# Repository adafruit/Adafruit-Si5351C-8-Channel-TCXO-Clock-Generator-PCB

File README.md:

## Adafruit Si5351C 8 Channel TCXO Clock Generator - 2.5KHz-200MHz - STEMMA QT PCB

<a href="http://www.adafruit.com/products/6534"><br/>
Click here to purchase one from the Adafruit shop</a>

PCB files for the Adafruit Si5351C 8 Channel TCXO Clock Generator - 2.5KHz-200MHz - STEMMA QT. 

Format is EagleCAD schematic and board layout
* https://www.adafruit.com/product/6534

### Description

Never hunt around for another crystal again, with the Si5351C clock generator breakout from Adafruit! This chip has a precision <b>temperature compensated (TCXO)</b> 25MHz crystal reference and internal PLL and dividers so it can generate just about any frequency, from 2.5 KHz up to 200 MHz on CLK0-CLK5, and about 20 kHz to 50 Mhz on CLK6 and CLK7.

The Si5351C clock generator is an I2C controller clock generator with eight outputs. It uses the onboard precision clock - or an external clock - to drive multiple PLL's and clock dividers using I2C instructions. By setting up the PLL and dividers you can create precise and arbitrary frequencies. There are eight independent outputs, and each one can have a different frequency. Outputs are 3Vpp by default but can be configured to be lower via the VDDA/B/C/D breakout pads. The outputs can be accessed either through a breadboard-friendly header or, for RF work, [optional edge-launch SMA connector](https://www.adafruit.com/product/1865) for alternating outputs - so 4 total. The edge launch SMA connectors are sold separately.

To get you going fast, we spun up a custom-made PCB in the [STEMMA QT form factor](https://www.adafruit.com/?q=stemma%20qt%20sensor), making it easy to interface with. The [STEMMA QT connectors](https://learn.adafruit.com/introducing-adafruit-stemma-qt/what-is-stemma-qt) on either side are compatible with the [SparkFun Qwiic](https://www.sparkfun.com/qwiic) I2C connectors. This allows you to make solderless connections between your development board and the Si5351 or to chain it with a wide range of other sensors and accessories using a [compatible cable](https://www.adafruit.com/?q=stemma%20qt%20cable). Onboard 3.3V LDO and level shifters means its ready for use with 3V or 5V power and logic!

[Best of all, we even have a great tutorial and library to get you started! Our code is designed for use with the Arduino-compatible microcontrollers and CircuitPython/Python](https://learn.adafruit.com/adafruit-si5351-clock-generator-breakout) using I2C support.

### License

Adafruit invests time and resources providing this open source design, please support Adafruit and open-source hardware by purchasing products from [Adafruit](https://www.adafruit.com)!

Designed by Limor Fried/Ladyada for Adafruit Industries.

Creative Commons Attribution/Share-Alike, all text above must be included in any redistribution. 
See license.txt for additional details.

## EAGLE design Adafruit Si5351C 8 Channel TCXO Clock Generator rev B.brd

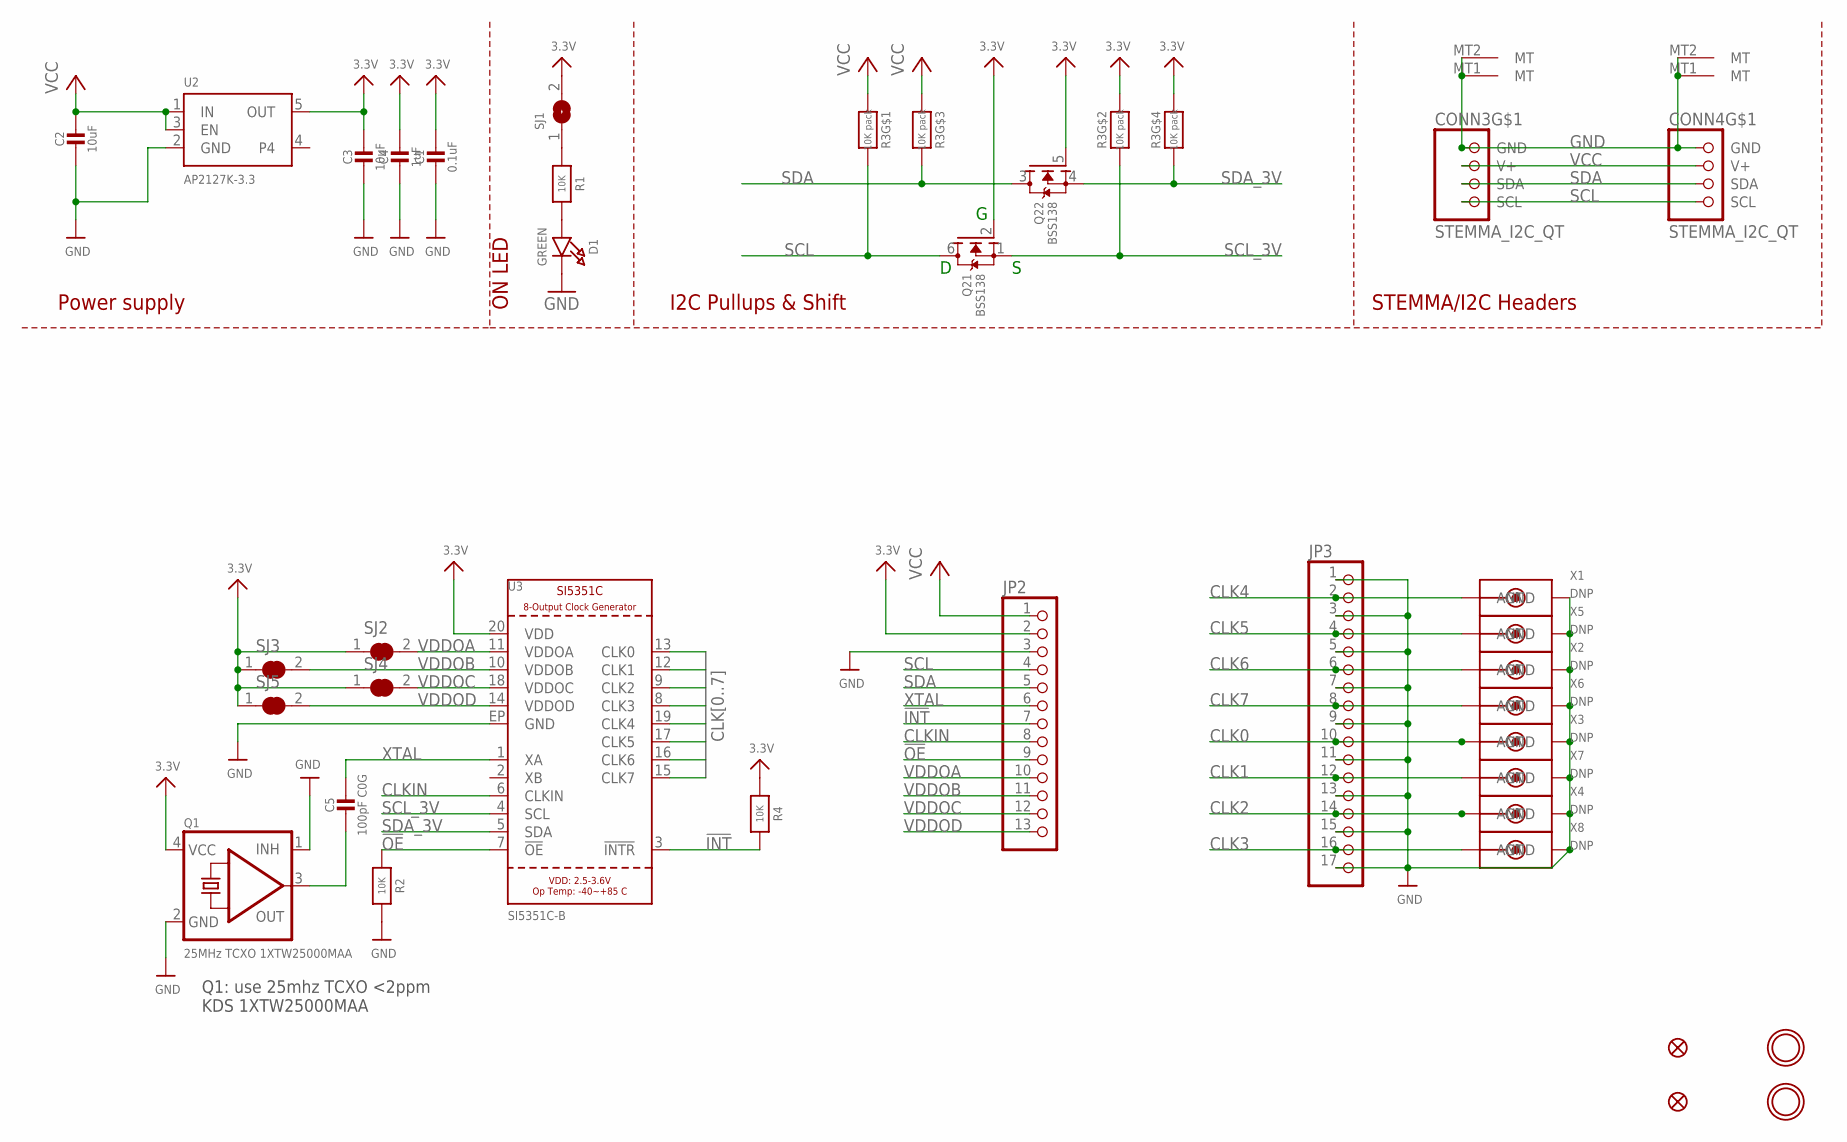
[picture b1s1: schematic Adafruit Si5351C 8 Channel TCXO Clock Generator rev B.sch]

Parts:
C1: 0.1uF; 0603-NO
C2, C3: 10uF; 0805-NO
C4: 1uF; 0603-NO
C5: 100pF C0G; 0603-NO
CONN3, CONN4: STEMMA_I2C_QT; JST_SH4
D1: GREEN; CHIPLED_0603_NOOUTLINE
FID3, FID4: FIDUCIAL_0.5MM
JP2: HEADER-1X13; 1X13_ROUND_70
JP3: HEADER-1X17; 1X17_ROUND70
Q1: 25MHz TCXO 1XTW25000MAA; OSC_3.2X2.5MM
Q2: BSS138; SOT363
R1, R2, R4: 10K; 0603-NO
R3: 10K pack; RESPACK_4X0603
SJ1: SOLDERJUMPERCLOSED; SOLDERJUMPER_CLOSEDWIRE
SJ2, SJ3, SJ4, SJ5: SOLDERJUMPER_CLOSED; SOLDERJUMPER_CLOSEDWIRE
U2: AP2127K-3.3; SOT23-5
U3: SI5351C-B; QFN20_4X4_0.5_SKY
U$19, U$21: MOUNTINGHOLE2.5; MOUNTINGHOLE_2.5_PLATED
X1, X2, X3, X4, X5, X6, X7, X8: DNP; SMA_EDGELAUNCH

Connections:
3.3V: C1.1, C3.1, C4.1, JP2.2, Q1.4 (VCC), Q2.2 (G), Q2.5 (G), R3.2 (1), R3.4 (1), R4.1, SJ1.2, SJ2.1, SJ3.1, SJ4.1, SJ5.1, U2.5 (OUT), U3.20 (VDD)
!INT: JP2.7, R4.2, U3.3 (!INTR)
!OE: JP2.9, R2.1, U3.7 (!OE)
CLK0: JP3.10, U3.13 (CLK0), X3.P (ANT)
CLK1: JP3.12, U3.12 (CLK1), X7.P (ANT)
CLK2: JP3.14, U3.9 (CLK2), X4.P (ANT)
CLK3: JP3.16, U3.8 (CLK3), X8.P (ANT)
CLK4: JP3.2, U3.19 (CLK4), X1.P (ANT)
CLK5: JP3.4, U3.17 (CLK5), X5.P (ANT)
CLK6: JP3.6, U3.16 (CLK6), X2.P (ANT)
CLK7: JP3.8, U3.15 (CLK7), X6.P (ANT)
CLKIN: JP2.8, U3.6 (CLKIN)
GND: C1.2, C2.2, C3.2, C4.2, CONN3.1 (GND), CONN3.MT1 (MT), CONN3.MT2 (MT), CONN4.1 (GND), CONN4.MT1 (MT), CONN4.MT2 (MT), D1.C, JP2.3, JP3.1, JP3.3, JP3.5, JP3.7, JP3.9, JP3.11, JP3.13, JP3.15, JP3.17, Q1.1 (INH), Q1.2 (GND), R2.2, U2.2 (GND), U3.EP (GND), X1.GND@1 (GND), X1.GND@2 (GND), X1.GND@3 (GND), X1.GND@4 (GND), X2.GND@1 (GND), X2.GND@2 (GND), X2.GND@3 (GND), X2.GND@4 (GND), X3.GND@1 (GND), X3.GND@2 (GND), X3.GND@3 (GND), X3.GND@4 (GND), X4.GND@1 (GND), X4.GND@2 (GND), X4.GND@3 (GND), X4.GND@4 (GND), X5.GND@1 (GND), X5.GND@2 (GND), X5.GND@3 (GND), X5.GND@4 (GND), X6.GND@1 (GND), X6.GND@2 (GND), X6.GND@3 (GND), X6.GND@4 (GND), X7.GND@1 (GND), X7.GND@2 (GND), X7.GND@3 (GND), X7.GND@4 (GND), X8.GND@1 (GND), X8.GND@2 (GND), X8.GND@3 (GND), X8.GND@4 (GND)
unnamed: D1.A, R1.2
unnamed: R1.1, SJ1.1
unnamed: C5.2, Q1.3 (OUT)
SCL: CONN3.4 (SCL), CONN4.4 (SCL), JP2.4, Q2.6 (D), R3.8 (2)
SCL_3V: Q2.1 (S), R3.7 (2), U3.4 (SCL)
SDA: CONN3.3 (SDA), CONN4.3 (SDA), JP2.5, Q2.3 (D), R3.6 (2)
SDA_3V: Q2.4 (S), R3.5 (2), U3.5 (SDA)
VCC: C2.1, CONN3.2 (V+), CONN4.2 (V+), JP2.1, R3.1, R3.3 (1), U2.1 (IN), U2.3 (EN)
VDDOA: JP2.10, SJ2.2, U3.11 (VDDOA)
VDDOB: JP2.11, SJ3.2, U3.10 (VDDOB)
VDDOC: JP2.12, SJ4.2, U3.18 (VDDOC)
VDDOD: JP2.13, SJ5.2, U3.14 (VDDOD)
XTAL: C5.1, JP2.6, U3.1 (XA)

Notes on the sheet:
I2C Pullups & Shift
STEMMA/I2C Headers
ON LED
Power supply
Q1: use 25mhz TCXO <2ppm KDS 1XTW25000MAA

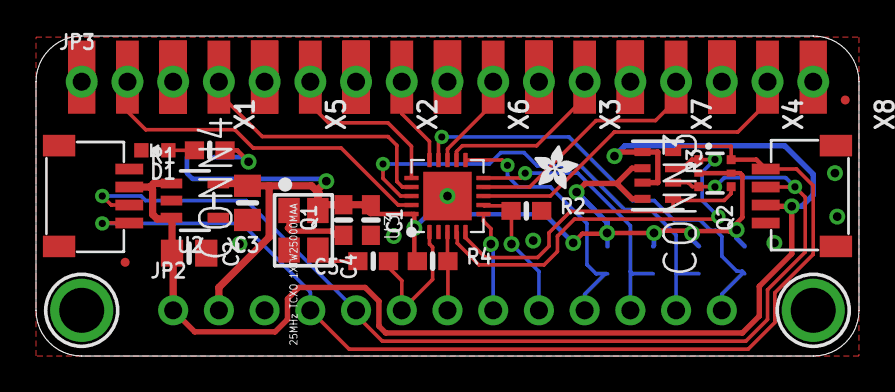
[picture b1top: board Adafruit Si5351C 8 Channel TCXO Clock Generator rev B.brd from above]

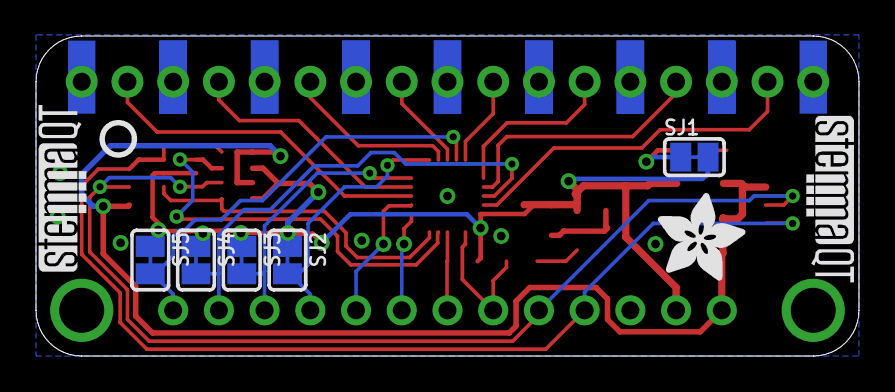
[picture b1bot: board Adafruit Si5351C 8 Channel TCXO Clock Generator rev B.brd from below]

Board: 2 copper layers, 45.7 x 17.8 mm, 82 parts (17 on the bottom side), 26 nets.

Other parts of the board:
PLABEL0: PLABEL0
PLABEL1: PLABEL1
PLABEL2: PLABEL2
PLABEL3: PLABEL3
PLABEL4: PLABEL4
PLABEL5: PLABEL5
PLABEL11: PLABEL11
PLABEL12: PLABEL12
PLABEL13: PLABEL13
PLABEL14, PLABEL15, PLABEL16, PLABEL17, PLABEL18, PLABEL19, PLABEL20, PLABEL21, PLABEL30: PLABEL14
PLABEL22: PLABEL22
PLABEL23: PLABEL23
PLABEL24: PLABEL24
PLABEL25: PLABEL25
PLABEL26: PLABEL26
PLABEL27: PLABEL27
PLABEL28: PLABEL28
PLABEL29: PLABEL29
PLABEL31: PLABEL31
PLABEL32: PLABEL32
PLABEL34: PLABEL34
PLABEL35: PLABEL35
PLABEL36: PLABEL36
PLABEL37: PLABEL37
PLABEL38: PLABEL38
PLABEL39: PLABEL39
PLABEL40: PLABEL40
PLABEL41: PLABEL41
PLABEL42: PLABEL42
PLABEL43: PLABEL43
PLABEL44: PLABEL44
PLABEL45: PLABEL45
PLABEL46: PLABEL46
PLABEL47: PLABEL47
U$4: ADAFRUIT_5MM
U$9: ADAFRUIT_2.5MM
U$25: PCBFEAT-REV-040
U$30, U$31: STEMMAQT

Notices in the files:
parts and their libraries:
microbuilder: This work is placed in the public domain, and may be freely used for commercial and non-commercial work with the following conditions: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
